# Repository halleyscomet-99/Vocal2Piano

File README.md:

# Vocal2Piano

A robot piano accompanist. A singer sings; a robot sitting on a real keyboard plays the piano part alongside. Two carriages (treble and bass) slide along the keys on stepper motors, each with 13 solenoid fingers.

The app runs in the browser: it loads a song (MIDI or sheet music) or turns a hummed tune into one, plans what the robot can reach and play, and streams it to the robot over USB during rehearsal. With Listen on, the piano follows the singer as it plays: it waits for each entrance, matches the singer's loudness, and moves to the key being sung.

## Repository

| Folder | What's in it |
|---|---|
| [`site/`](site) | The app: React + TypeScript, runs in Chrome or Edge, no install. Start here |
| [`software/`](software) | Offline Python tools: statistics from music datasets (McGill Billboard, POP909) and transcribers for local scores and recordings |
| [`firmware/`](firmware) | Teensy 4.1 firmware (PlatformIO): carriages, solenoids and safety limits, driven by the app over USB ([`PROTOCOL.md`](firmware/PROTOCOL.md)). Its README has the bring-up steps |
| [`hardware/CAD/`](hardware/CAD) | Fusion 360 models of the robot: carriages, fingers, mounts |
| [`hardware/PCB/`](hardware/PCB) | KiCad boards: `C0nTrollER` (Teensy, stepper drivers, power) and `PLAyeRs` (13 solenoid channels each), with fabrication files |
| [`legacy/`](legacy) | The first version (Python pipeline, Max/MSP patch, old firmware), kept for reference |

## Run

```bash
cd site
npm install
npm run dev
```

## Local songs

Scores and recordings to transcribe go in `software/input/`, and the results in `site/local/`. Both folders are git-ignored: transcriptions of other people's songs are for private practice, not for publishing.

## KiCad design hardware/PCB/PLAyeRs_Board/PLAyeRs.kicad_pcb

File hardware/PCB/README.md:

# PCB： Design

| Board | Role | Size | Qty |
|---|---|---|---|
| [**C0nTrollER**](C0nTrollER_Board/) | Main controller: Teensy 4.1, two stepper drivers, power input and protection, 5 V rail | 134.7 × 71.2 mm | 1 |
| [**PLAyeRs**](PLAyeRs_Board/) | Solenoid driver: 13 channels driven by a PCA9685 over I²C | 230.1 × 40.1 mm | 2 (Treble + Bass) |

## System Architecture

```
        12 V DC (5 A supply, barrel jack)
              │
   ┌──────────▼────────────────────────────────────────┐
   │ C0nTrollER                                        │
   │  5 A fuse → SMBJ16A TVS → PMOS reverse-polarity   │
   │  → 12 V rail (4700 µF bulk)                       │
   │  MP1584 buck → 5 V                                │
   │  Teensy 4.1 ─ STEP/DIR/EN ─► TMC2209 ×2 ─► NEMA17 ×2
   │             ◄─ ENDSTOP ×2                         │
   │             ─ I²C (SDA/SCL, 4.7 kΩ pull-ups) ─┐   │
   └───────────────────────────────────────────────┼───┘
         7-pin JST-XH (TREBLE)        7-pin JST-XH (BASS)
                 ▼                              ▼
          ┌─────────────┐                ┌─────────────┐
          │ PLAyeRs     │                │ PLAyeRs     │
          │ PCA9685 0x41│                │ PCA9685 0x40│
          │ 13× IRLZ34N │                │ 13× IRLZ34N │
          └──────┬──────┘                └──────┬──────┘
           13 solenoids                    13 solenoids
```

Both PLAyeRs boards share one I²C bus. The board with the A0 solder jumper bridged is `0x41` (Treble); the one without it is `0x40` (Bass).

### Why these parts
- **One MOSFET per key.** A solenoid needs 12 V at about 0.4 A, far more than any logic pin can supply, so each key has its own logic-level N-MOSFET (IRLZ34N) working as a low-side switch.
- **PCA9685.** It gives 16 PWM outputs over two I²C wires. One chip per player board covers all 13 keys, and the PWM can vary how hard a key is struck.
- **TMC2209.** A very quiet stepper driver, which matters because the robot sits next to a microphone. The Teensy only sends STEP / DIR / EN.
- **MP1584 buck.** Steps 12 V down to 5 V efficiently. A linear regulator would turn the difference into heat.
- **Teensy 4.1.** Fast, with plenty of pins and native USB MIDI for the music software.
- **4 layers.** The inner layers are planes: In1 = GNDPWR, In2 = +12 V. They give wide, low-resistance paths for the solenoid and motor current and keep motor noise away from the logic.
- **Double-sided placement on PLAyeRs.** It keeps the long, narrow board compact. C0nTrollER has every part on the top side.

---

## C0nTrollER Board

[Schematic PDF](C0nTrollER_Board/C0nTrollER.pdf) · [3D model](C0nTrollER_Board/C0nTrollER.step) · [Gerbers](C0nTrollER_Board/output/output.zip)

### Power path
1. 12 V barrel jack (CUI PJ-102AH; the connector is rated 5 A).
2. 5 A slow-blow fuse in a 5×20 mm holder (F1).
3. SMBJ16A TVS diode (CR1) clamps voltage spikes.
4. P-MOSFET (Q1, with gate Zener D1) blocks reverse polarity.
5. 4700 µF bulk capacitor (C1, rated 16 V or more; mind the polarity) keeps 12 V steady when the motors and solenoids switch.
6. MP1584 buck module makes 5 V for the Teensy and the PLAyeRs logic.

> **Before first power-up:** with the Teensy removed, adjust the MP1584 output to 5.0 V. Then cut the VIN–VUSB trace on the underside of the Teensy. Otherwise USB 5 V and the board's 5 V rail are tied together and fight each other.

### Teensy 4.1 pin map

| Function | Treble | Bass |
|---|---|---|
| STEP | 5 | 2 |
| DIR | 6 | 3 |
| EN (active LOW) | 7 | 4 |
| ENDSTOP (`INPUT_PULLUP`, pressed = LOW) | 10 | 8 |

I²C uses `Wire`: SDA = pin 18, SCL = pin 19. The TMC2209 UART is not used; motor current is set with each driver's Vref potentiometer.

## PLAyeRs Board

<!-- TODO: photo of the assembled board, ideally on the carriage with solenoids wired -->

[Schematic PDF](PLAyeRs_Board/PLAyeRs.pdf) · [3D model](PLAyeRs_Board/PLAyeRs.step) · [Gerbers](PLAyeRs_Board/output/output.zip)

### One solenoid channel

```
PCA9685 PWM ─ 100 Ω ─┬─ Gate ┐
                     └─ 10 kΩ ─ GNDPWR      IRLZ34N
12 V ─┬─ solenoid ───────────── Drain       Source ─ GNDPWR
      ├─ SS14 (cathode to 12 V, anode to Drain)   flyback
      └─ 680 Ω ─ LED ───────── Drain         lights while the solenoid is on
```

- The 100 Ω gate resistor limits switching current. The 10 kΩ pull-down holds the MOSFET off when the PWM pin isn't being driven.
- The SS14 diode absorbs the inductive kick when the coil switches off.
- The status LED lights when the MOSFET pulls the drain low, so every strike is visible.
- With no solenoid connected, the drain floats at about 9.8 V; this is normal. With a solenoid connected, the drain idles at about 12 V.

### Solenoid
JF-1039(B): 12 V, about 0.4 A, 10 mm stroke, 25 N at full closure. The force is much lower when the plunger is far from closed. Don't keep a solenoid energized for more than about 2 s.

### Power budget
With all 13 channels on at once, one board draws 13 × 0.4 A ≈ 5.2 A, so both boards together draw about 10 A. A 5 A supply cannot sustain that. Firmware must therefore limit how many fingers fire at the same time: a few at once, with short pulses. In normal playing, strikes last 30–150 ms.

## Manufacturing

| Parameter | Value |
|---|---|
| Layers | 4 (F.Cu / In1.Cu GNDPWR / In2.Cu +12 V / B.Cu) |
| Thickness | 1.6 mm |
| Copper | 1 oz outer (35 µm) |
| Fab | JLCPCB (upload `output/output.zip` from each board folder) |

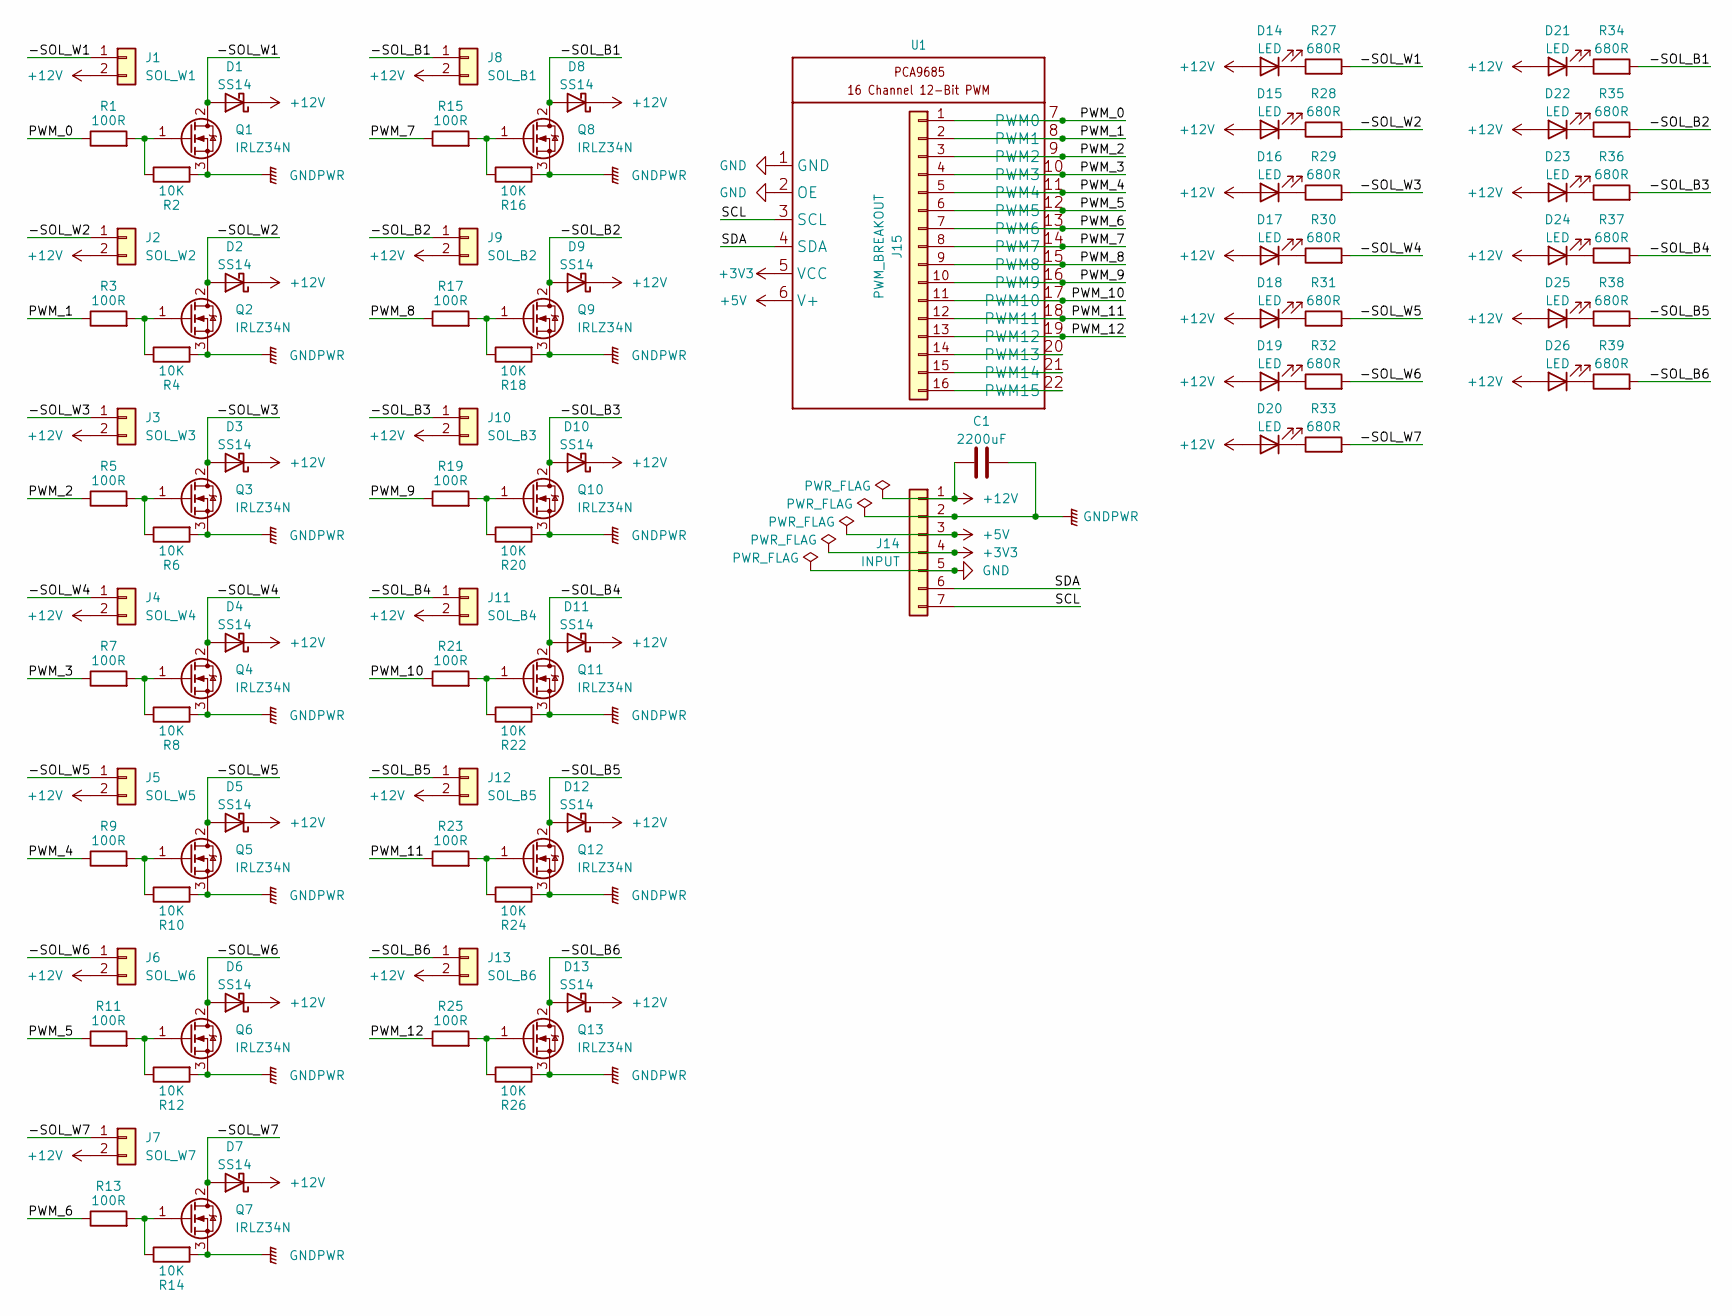
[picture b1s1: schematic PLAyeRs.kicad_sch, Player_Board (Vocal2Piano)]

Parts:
C1: 2200uF; CP_Radial_D16.0mm_P7.50mm
D1, D2, D3, D4, D5, D6, D7, D8, D9, D10, D11, D12, D13: SS14; D_SMA
D14, D15, D16, D17, D18, D19, D20, D21, D22, D23, D24, D25, D26: LED; LED_D5.0mm
J1: SOL_W1; JST_XH_B2B-XH-A_1x02_P2.50mm_Vertical
J2: SOL_W2; JST_XH_B2B-XH-A_1x02_P2.50mm_Vertical
J3: SOL_W3; JST_XH_B2B-XH-A_1x02_P2.50mm_Vertical
J4: SOL_W4; JST_XH_B2B-XH-A_1x02_P2.50mm_Vertical
J5: SOL_W5; JST_XH_B2B-XH-A_1x02_P2.50mm_Vertical
J6: SOL_W6; JST_XH_B2B-XH-A_1x02_P2.50mm_Vertical
J7: SOL_W7; JST_XH_B2B-XH-A_1x02_P2.50mm_Vertical
J8: SOL_B1; JST_XH_B2B-XH-A_1x02_P2.50mm_Vertical
J9: SOL_B2; JST_XH_B2B-XH-A_1x02_P2.50mm_Vertical
J10: SOL_B3; JST_XH_B2B-XH-A_1x02_P2.50mm_Vertical
J11: SOL_B4; JST_XH_B2B-XH-A_1x02_P2.50mm_Vertical
J12: SOL_B5; JST_XH_B2B-XH-A_1x02_P2.50mm_Vertical
J13: SOL_B6; JST_XH_B2B-XH-A_1x02_P2.50mm_Vertical
J14: INPUT; JST_XH_B7B-XH-A_1x07_P2.50mm_Vertical
J15: PWM_BREAKOUT; PinSocket_1x16_P2.54mm_Vertical
Q1, Q2, Q3, Q4, Q5, Q6, Q7, Q8, Q9, Q10, Q11, Q12, Q13: IRLZ34N; TO-220-3_Vertical
R1, R3, R5, R7, R9, R11, R13, R15, R17, R19, R21, R23, R25: 100R; R_0805_2012Metric
R2, R4, R6, R8, R10, R12, R14, R16, R18, R20, R22, R24, R26: 10K; R_0805_2012Metric
R27, R28, R29, R30, R31, R32, R33, R34, R35, R36, R37, R38, R39: 680R; R_0805_2012Metric
U1: Adafruit PCA9685 rev C

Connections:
+3V3: J14.4, U1.5 (VCC)
+5V: J14.3, U1.6 (V+)
+12V: C1.1, D1.1 (K), D2.1 (K), D3.1 (K), D4.1 (K), D5.1 (K), D6.1 (K), D7.1 (K), D8.1 (K), D9.1 (K), D10.1 (K), D11.1 (K), D12.1 (K), D13.1 (K), D14.2 (A), D15.2 (A), D16.2 (A), D17.2 (A), D18.2 (A), D19.2 (A), D20.2 (A), D21.2 (A), D22.2 (A), D23.2 (A), D24.2 (A), D25.2 (A), D26.2 (A), J1.2, J2.2, J3.2, J4.2, J5.2, J6.2, J7.2, J8.2, J9.2, J10.2, J11.2, J12.2, J13.2, J14.1
/-SOL_B1: D8.2 (A), J8.1, Q8.2 (D), R34.2
/-SOL_B2: D9.2 (A), J9.1, Q9.2 (D), R35.2
/-SOL_B3: D10.2 (A), J10.1, Q10.2 (D), R36.2
/-SOL_B4: D11.2 (A), J11.1, Q11.2 (D), R37.2
/-SOL_B5: D12.2 (A), J12.1, Q12.2 (D), R38.2
/-SOL_B6: D13.2 (A), J13.1, Q13.2 (D), R39.2
/-SOL_W1: D1.2 (A), J1.1, Q1.2 (D), R27.2
/-SOL_W2: D2.2 (A), J2.1, Q2.2 (D), R28.2
/-SOL_W3: D3.2 (A), J3.1, Q3.2 (D), R29.2
/-SOL_W4: D4.2 (A), J4.1, Q4.2 (D), R30.2
/-SOL_W5: D5.2 (A), J5.1, Q5.2 (D), R31.2
/-SOL_W6: D6.2 (A), J6.1, Q6.2 (D), R32.2
/-SOL_W7: D7.2 (A), J7.1, Q7.2 (D), R33.2
/PWM_0: J15.1, R1.1, U1.7 (PWM0)
/PWM_1: J15.2, R3.1, U1.8 (PWM1)
/PWM_2: J15.3, R5.1, U1.9 (PWM2)
/PWM_3: J15.4, R7.1, U1.10 (PWM3)
/PWM_4: J15.5, R9.1, U1.11 (PWM4)
/PWM_5: J15.6, R11.1, U1.12 (PWM5)
/PWM_6: J15.7, R13.1, U1.13 (PWM6)
/PWM_7: J15.8, R15.1, U1.14 (PWM7)
/PWM_8: J15.9, R17.1, U1.15 (PWM8)
/PWM_9: J15.10, R19.1, U1.16 (PWM9)
/PWM_10: J15.11, R21.1, U1.17 (PWM10)
/PWM_11: J15.12, R23.1, U1.18 (PWM11)
/PWM_12: J15.13, R25.1, U1.19 (PWM12)
/SCL: J14.7, U1.3 (SCL)
/SDA: J14.6, U1.4 (SDA)
GND: J14.5, U1.1 (GND), U1.2 (OE)
GNDPWR: C1.2, J14.2, Q1.3 (S), Q2.3 (S), Q3.3 (S), Q4.3 (S), Q5.3 (S), Q6.3 (S), Q7.3 (S), Q8.3 (S), Q9.3 (S), Q10.3 (S), Q11.3 (S), Q12.3 (S), Q13.3 (S), R2.2, R4.2, R6.2, R8.2, R10.2, R12.2, R14.2, R16.2, R18.2, R20.2, R22.2, R24.2, R26.2
unnamed: D14.1 (K), R27.1
unnamed: D15.1 (K), R28.1
unnamed: D16.1 (K), R29.1
unnamed: D17.1 (K), R30.1
unnamed: D18.1 (K), R31.1
unnamed: D19.1 (K), R32.1
unnamed: D20.1 (K), R33.1
unnamed: D21.1 (K), R34.1
unnamed: D22.1 (K), R35.1
unnamed: D23.1 (K), R36.1
unnamed: D24.1 (K), R37.1
unnamed: D25.1 (K), R38.1
unnamed: D26.1 (K), R39.1
unnamed: J15.14, U1.20 (PWM13)
unnamed: J15.15, U1.21 (PWM14)
unnamed: J15.16, U1.22 (PWM15)
unnamed: Q1.1 (G), R1.2, R2.1
unnamed: Q2.1 (G), R3.2, R4.1
unnamed: Q3.1 (G), R5.2, R6.1
unnamed: Q4.1 (G), R7.2, R8.1
unnamed: Q5.1 (G), R9.2, R10.1
unnamed: Q6.1 (G), R11.2, R12.1
unnamed: Q7.1 (G), R13.2, R14.1
unnamed: Q8.1 (G), R15.2, R16.1
unnamed: Q9.1 (G), R17.2, R18.1
unnamed: Q10.1 (G), R19.2, R20.1
unnamed: Q11.1 (G), R21.2, R22.1
unnamed: Q12.1 (G), R23.2, R24.1
unnamed: Q13.1 (G), R25.2, R26.1

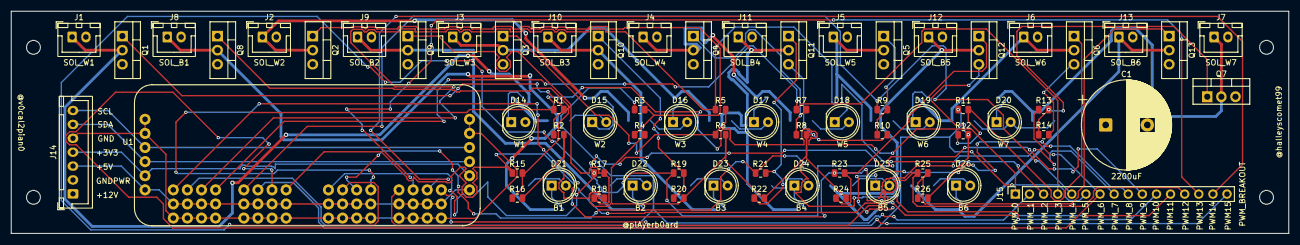
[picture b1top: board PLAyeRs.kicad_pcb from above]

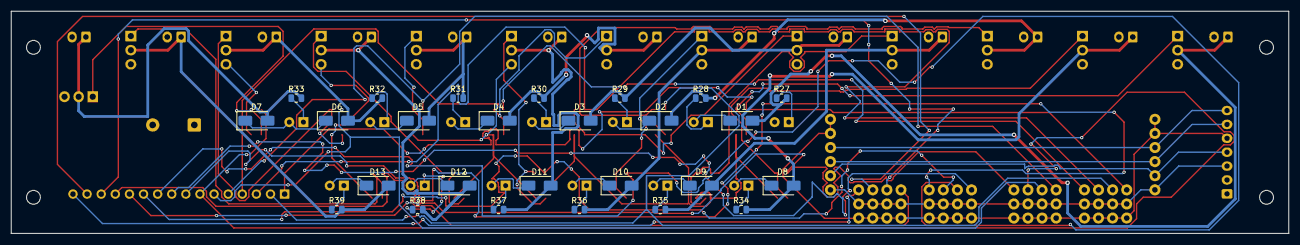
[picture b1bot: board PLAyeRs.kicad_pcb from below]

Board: 4 copper layers, 230.0 x 40.0 mm, 95 parts (26 on the bottom side), 62 nets.

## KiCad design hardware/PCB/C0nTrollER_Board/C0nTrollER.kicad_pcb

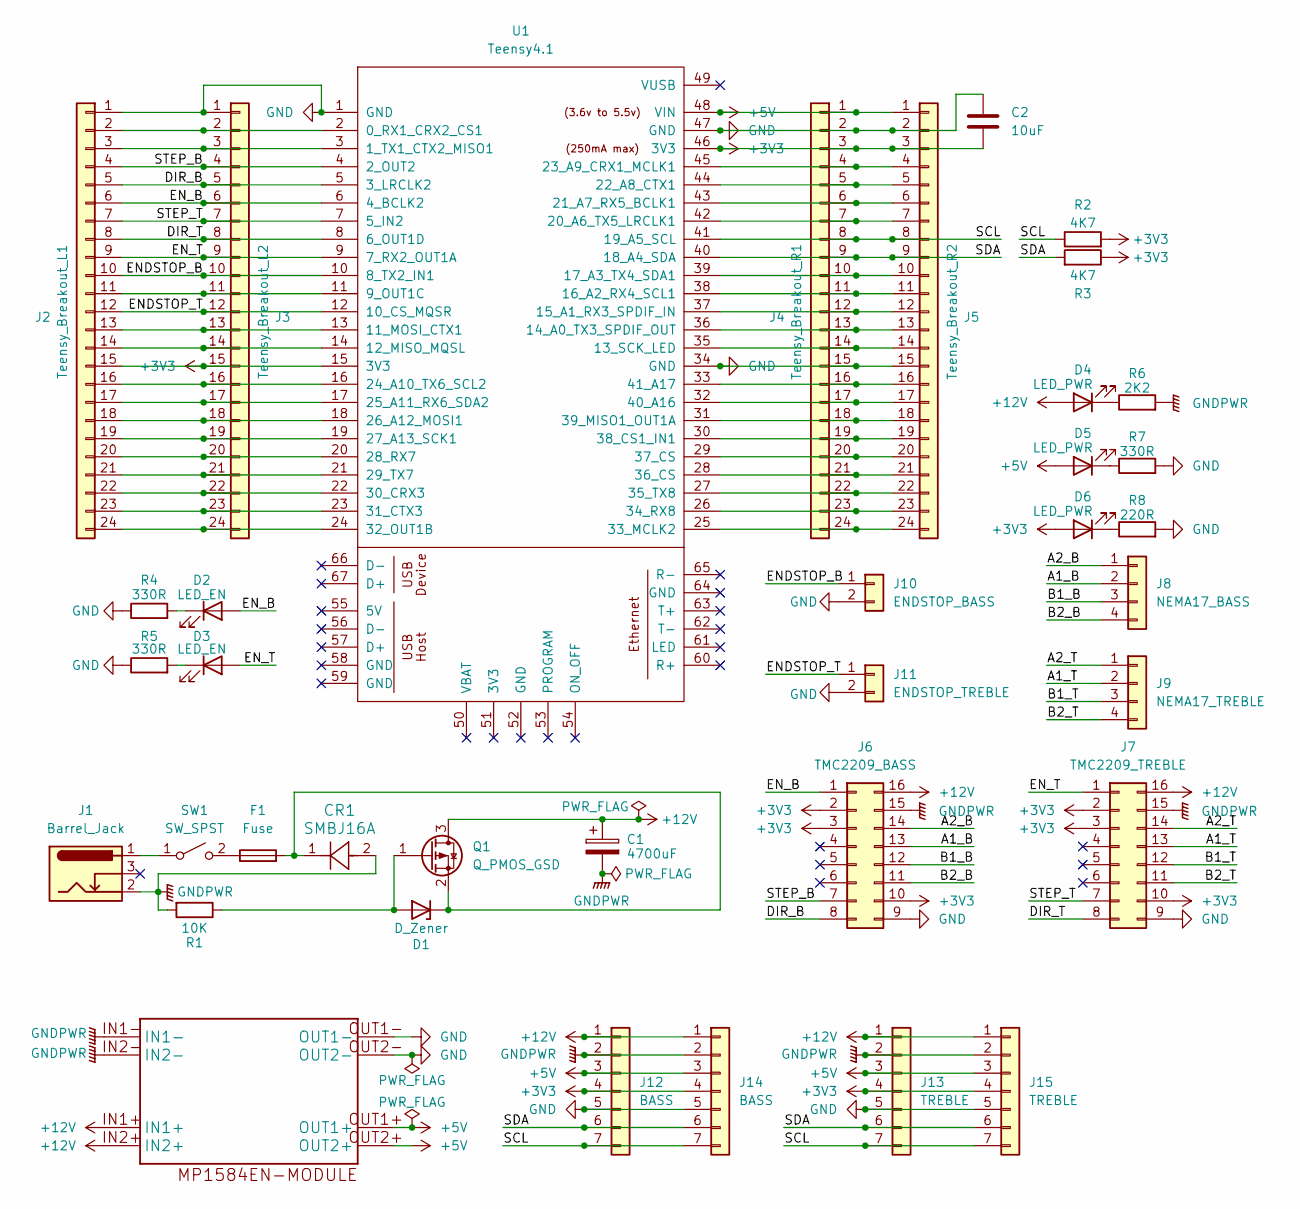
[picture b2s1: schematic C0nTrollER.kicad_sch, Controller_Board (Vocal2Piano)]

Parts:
C1: 4700uF; CP_Radial_D10.0mm_P5.00mm
C2: 10uF; C_0805_2012Metric
CR1: SMBJ16A; SMBJSeries_LTF
D1: D_Zener; D_DO-41_SOD81_P10.16mm_Horizontal
D2, D3: LED_EN; LED_0805_2012Metric
D4, D5, D6: LED_PWR; LED_0805_2012Metric
F1: Fuse; Fuseholder_Cylinder-5x20mm_Bulgin_FX0457_Horizontal_Closed
J1: Barrel_Jack; BarrelJack_CUI_PJ-102AH_Horizontal
J2: Teensy_Breakout_L1; PinSocket_1x24_P2.54mm_Vertical
J3: Teensy_Breakout_L2; PinSocket_1x24_P2.54mm_Vertical
J4: Teensy_Breakout_R1; PinSocket_1x24_P2.54mm_Vertical
J5: Teensy_Breakout_R2; PinSocket_1x24_P2.54mm_Vertical
J6: TMC2209_BASS; Pololu_Breakout-16_15.2x20.3mm
J7: TMC2209_TREBLE; Pololu_Breakout-16_15.2x20.3mm
J8: NEMA17_BASS; PinSocket_1x04_P2.54mm_Vertical
J9: NEMA17_TREBLE; PinSocket_1x04_P2.54mm_Vertical
J10: ENDSTOP_BASS; PinSocket_1x02_P2.54mm_Vertical
J11: ENDSTOP_TREBLE; PinSocket_1x02_P2.54mm_Vertical
J12: BASS; JST_XH_B7B-XH-A_1x07_P2.50mm_Vertical
J13: TREBLE; JST_XH_B7B-XH-A_1x07_P2.50mm_Vertical
J14: BASS; PinSocket_1x07_P2.54mm_Vertical
J15: TREBLE; PinSocket_1x07_P2.54mm_Vertical
MP1584: DSUN_NEW
Q1: Q_PMOS_GSD; SOT-23
R1: 10K; R_0805_2012Metric
R2, R3: 4K7; R_0805_2012Metric
R4, R5, R7: 330R; R_0805_2012Metric
R6: 2K2; R_0805_2012Metric
R8: 220R; R_0805_2012Metric
SW1: SW_SPST; PinSocket_1x02_P2.54mm_Vertical
U1: Teensy4.1; Teensy41

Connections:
+3V3: C2.2, D6.2 (A), J2.15, J3.15, J4.3, J5.3, J6.2, J6.3, J6.10, J7.2, J7.3, J7.10, J12.4, J13.4, J14.4, J15.4, R2.2, R3.1, U1.15 (3V3), U1.46 (3V3)
+5V: D5.2 (A), J4.1, J5.1, J12.3, J13.3, J14.3, J15.3, MP1584.OUT1+, MP1584.OUT2+, U1.48 (VIN)
+12V: C1.1, D4.2 (A), J6.16, J7.16, J12.1, J13.1, J14.1, J15.1, MP1584.IN1+, MP1584.IN2+, Q1.3 (D)
/A1_B: J6.13, J8.2
/A1_T: J7.13, J9.2
/A2_B: J6.14, J8.1
/A2_T: J7.14, J9.1
/B1_B: J6.12, J8.3
/B1_T: J7.12, J9.3
/B2_B: J6.11, J8.4
/B2_T: J7.11, J9.4
/DIR_B: J2.5, J3.5, J6.8, U1.5 (3_LRCLK2)
/DIR_T: J2.8, J3.8, J7.8, U1.8 (6_OUT1D)
/ENDSTOP_B: J2.10, J3.10, J10.1, U1.10 (8_TX2_IN1)
/ENDSTOP_T: J2.12, J3.12, J11.1, U1.12 (10_CS_MQSR)
/EN_B: D2.2 (A), J2.6, J3.6, J6.1, U1.6 (4_BCLK2)
/EN_T: D3.2 (A), J2.9, J3.9, J7.1, U1.9 (7_RX2_OUT1A)
/SCL: J4.8, J5.8, J12.7, J13.7, J14.7, J15.7, R2.1, U1.41 (19_A5_SCL)
/SDA: J4.9, J5.9, J12.6, J13.6, J14.6, J15.6, R3.2, U1.40 (18_A4_SDA)
/STEP_B: J2.4, J3.4, J6.7, U1.4 (2_OUT2)
/STEP_T: J2.7, J3.7, J7.7, U1.7 (5_IN2)
GND: C2.1, J2.1, J3.1, J4.2, J4.15, J5.2, J5.15, J6.9, J7.9, J10.2, J11.2, J12.5, J13.5, J14.5, J15.5, MP1584.OUT1-, MP1584.OUT2-, R4.1, R5.1, R7.2, R8.2, U1.1 (GND), U1.34 (GND), U1.47 (GND)
GNDPWR: C1.2, CR1.2, J1.2, J6.15, J7.15, J12.2, J13.2, J14.2, J15.2, MP1584.IN1-, MP1584.IN2-, R1.2, R6.2
unnamed: D1.2 (A), Q1.1 (G), R1.1
unnamed: CR1.1, D1.1 (K), F1.2, Q1.2 (S)
unnamed: D2.1 (K), R4.2
unnamed: D3.1 (K), R5.2
unnamed: D4.1 (K), R6.1
unnamed: D5.1 (K), R7.1
unnamed: D6.1 (K), R8.1
unnamed: J2.2, J3.2, U1.2 (0_RX1_CRX2_CS1)
unnamed: J2.3, J3.3, U1.3 (1_TX1_CTX2_MISO1)
unnamed: J2.11, J3.11, U1.11 (9_OUT1C)
unnamed: J2.13, J3.13, U1.13 (11_MOSI_CTX1)
unnamed: J2.14, J3.14, U1.14 (12_MISO_MQSL)
unnamed: J2.16, J3.16, U1.16 (24_A10_TX6_SCL2)
unnamed: J2.17, J3.17, U1.17 (25_A11_RX6_SDA2)
unnamed: J2.18, J3.18, U1.18 (26_A12_MOSI1)
unnamed: J2.19, J3.19, U1.19 (27_A13_SCK1)
unnamed: J2.20, J3.20, U1.20 (28_RX7)
unnamed: J2.21, J3.21, U1.21 (29_TX7)
unnamed: J2.22, J3.22, U1.22 (30_CRX3)
unnamed: J2.23, J3.23, U1.23 (31_CTX3)
unnamed: J2.24, J3.24, U1.24 (32_OUT1B)
unnamed: J4.4, J5.4, U1.45 (23_A9_CRX1_MCLK1)
unnamed: J4.5, J5.5, U1.44 (22_A8_CTX1)
unnamed: J4.6, J5.6, U1.43 (21_A7_RX5_BCLK1)
unnamed: J4.7, J5.7, U1.42 (20_A6_TX5_LRCLK1)
unnamed: J4.10, J5.10, U1.39 (17_A3_TX4_SDA1)
unnamed: J4.11, J5.11, U1.38 (16_A2_RX4_SCL1)
unnamed: J4.12, J5.12, U1.37 (15_A1_RX3_SPDIF_IN)
unnamed: J4.13, J5.13, U1.36 (14_A0_TX3_SPDIF_OUT)
unnamed: J4.14, J5.14, U1.35 (13_SCK_LED)
unnamed: J4.16, J5.16, U1.33 (41_A17)
unnamed: J4.17, J5.17, U1.32 (40_A16)
unnamed: J4.18, J5.18, U1.31 (39_MISO1_OUT1A)
unnamed: J4.19, J5.19, U1.30 (38_CS1_IN1)
unnamed: J4.20, J5.20, U1.29 (37_CS)
unnamed: J4.21, J5.21, U1.28 (36_CS)
unnamed: J4.22, J5.22, U1.27 (35_TX8)
unnamed: J4.23, J5.23, U1.26 (34_RX8)
unnamed: J4.24, J5.24, U1.25 (33_MCLK2)
unnamed: J1.1, SW1.1 (A)
unnamed: F1.1, SW1.2 (B)

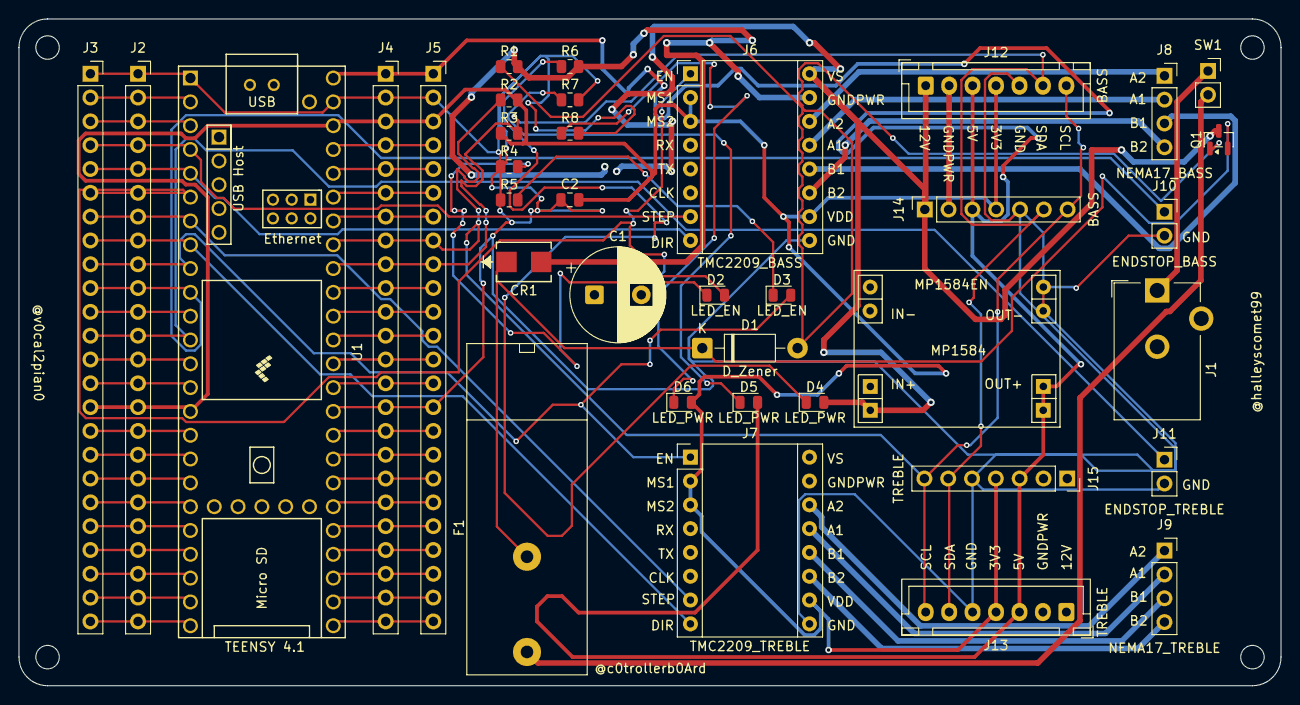
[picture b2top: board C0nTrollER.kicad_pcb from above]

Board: 4 copper layers, 134.6 x 71.1 mm, 37 parts (0 on the bottom side), 64 nets.

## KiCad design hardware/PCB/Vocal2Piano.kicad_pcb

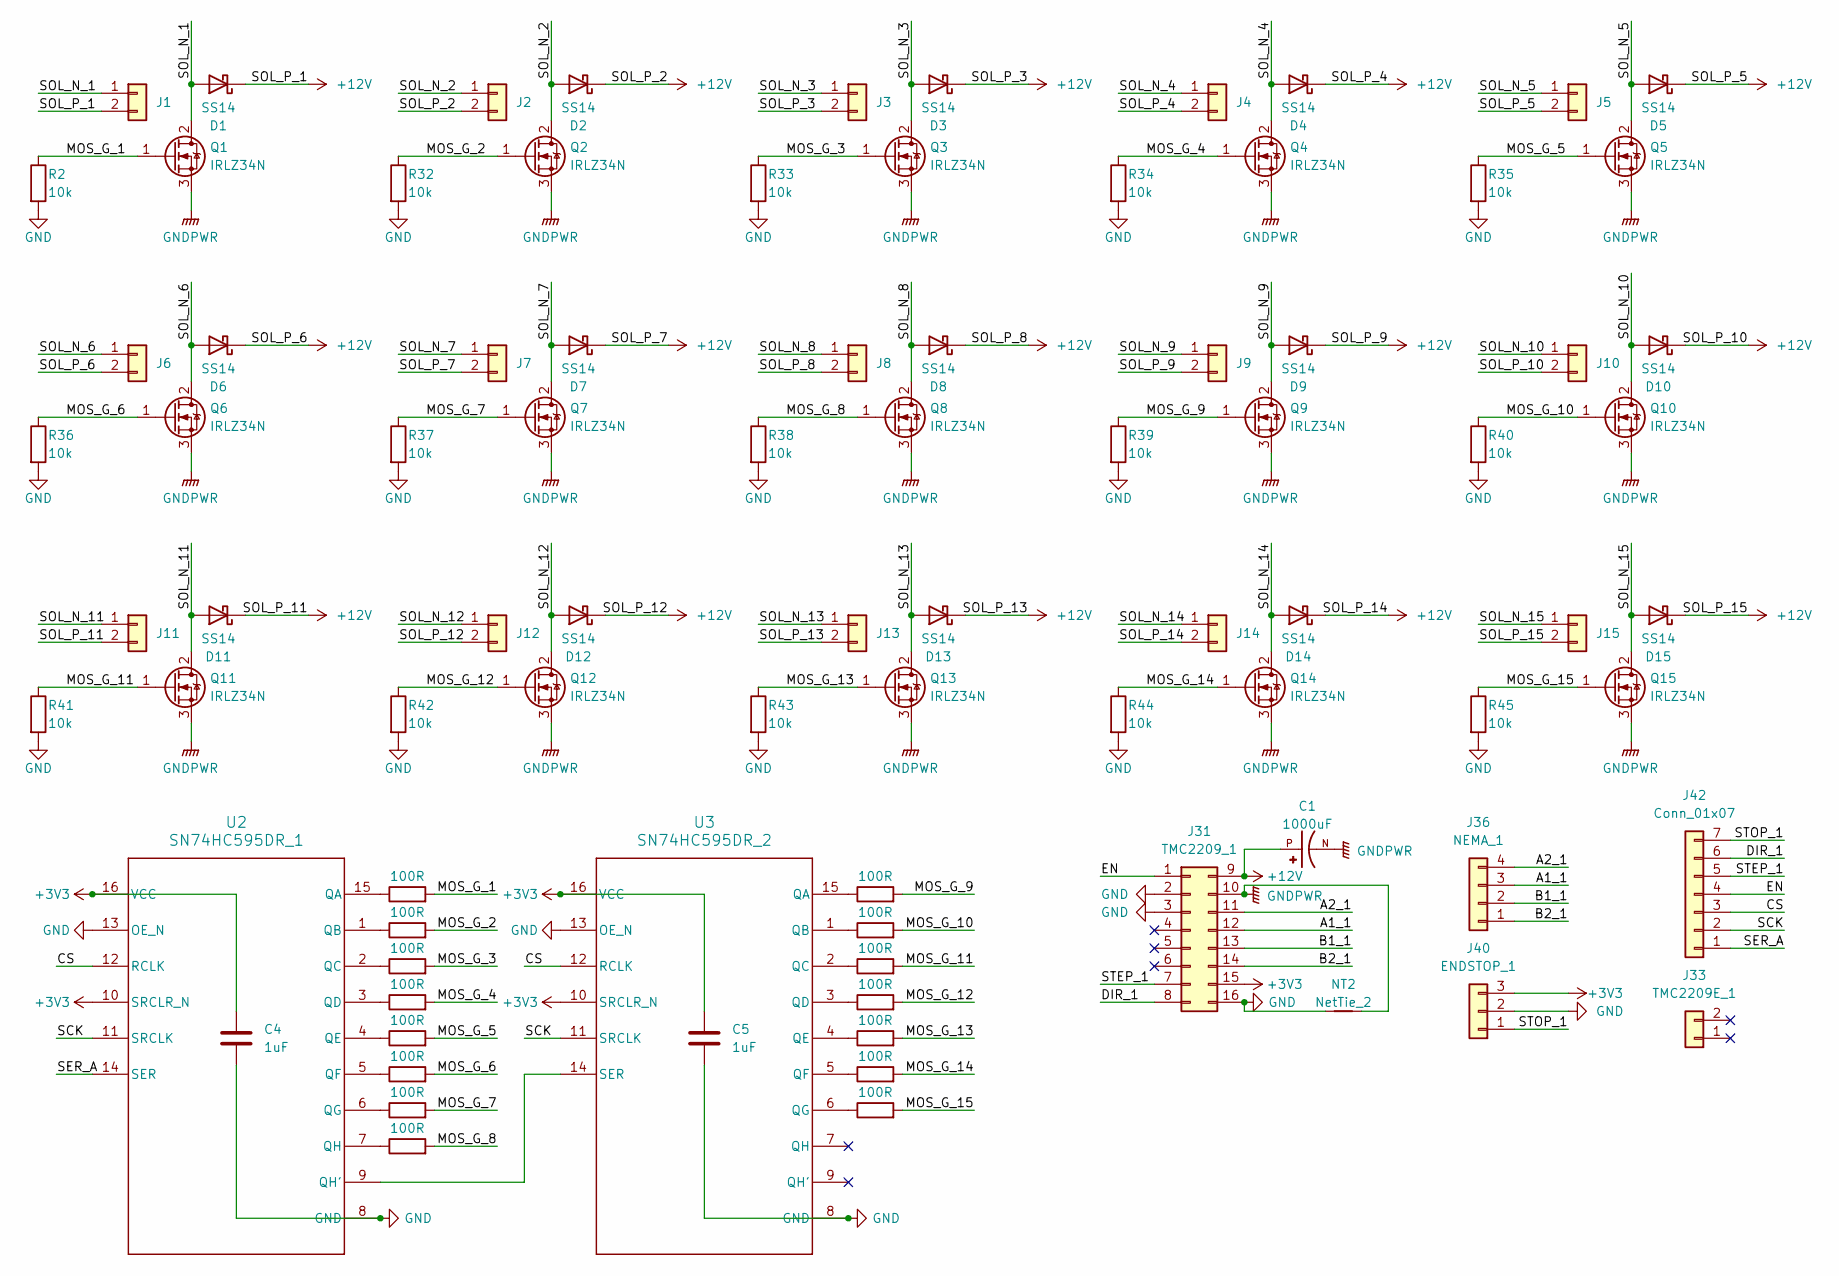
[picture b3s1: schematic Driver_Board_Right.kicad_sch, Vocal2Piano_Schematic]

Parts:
C1: 1000uF; CAPPRD500W60D1250H2000; PARTREV 20-DEC-19
C4, C5: 1uF; C_0805_2012Metric
D1, D2, D3, D4, D5, D6, D7, D8, D9, D10, D11, D12, D13, D14, D15: SS14; D_SMA
J1, J2, J3, J4, J5, J6, J7, J8, J9, J10, J11, J12, J13, J14, J15: Conn_01x02; PinSocket_1x02_P2.54mm_Vertical
J31: TMC2209_1; Pololu_Breakout-16_15.2x20.3mm
J33: TMC2209E_1; PinSocket_1x02_P2.54mm_Vertical
J36: NEMA_1; PinHeader_1x04_P2.54mm_Vertical
J40: ENDSTOP_1; JST_XH_B3B-XH-A_1x03_P2.50mm_Vertical
J42: Conn_01x07; PinSocket_1x07_P2.54mm_Vertical
NT2: NetTie_2; NetTie-2_SMD_Pad0.5mm
Q1, Q2, Q3, Q4, Q5, Q6, Q7, Q8, Q9, Q10, Q11, Q12, Q13, Q14, Q15: IRLZ34N; TO-220-3_Vertical
R1, R3, R4, R5, R6, R7, R8, R9, R10, R11, R12, R13, R14, R15, R16: 100R; R_0805_2012Metric
R2, R32, R33, R34, R35, R36, R37, R38, R39, R40, R41, R42, R43, R44, R45: 10k; R_0805_2012Metric
U2: SN74HC595DR_1; D0016A_N
U3: SN74HC595DR_2; D0016A_N

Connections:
+3V3: C4.1, C5.1, J31.15 (VDD), J40.3, U2.10 (SRCLR_N), U2.16 (VCC), U3.10 (SRCLR_N), U3.16 (VCC); also elsewhere on the board
+12V: C1.P, D1.1 (K), D2.1 (K), D3.1 (K), D4.1 (K), D5.1 (K), D6.1 (K), D7.1 (K), D8.1 (K), D9.1 (K), D10.1 (K), D11.1 (K), D12.1 (K), D13.1 (K), D14.1 (K), D15.1 (K), J1.2, J2.2, J3.2, J4.2, J5.2, J6.2, J7.2, J8.2, J9.2, J10.2, J11.2, J12.2, J13.2, J14.2, J15.2, J31.9 (VM); also elsewhere on the board
/Driver_Board_Right/A1_1: J31.12 (A1), J36.3
/Driver_Board_Right/A2_1: J31.11 (A2), J36.4
/Driver_Board_Right/B1_1: J31.13 (B1), J36.2
/Driver_Board_Right/B2_1: J31.14 (B2), J36.1
/Driver_Board_Right/CS: J42.3, U2.12 (RCLK), U3.12 (RCLK)
/Driver_Board_Right/DIR_1: J31.8 (DIR), J42.6
/Driver_Board_Right/EN: J31.1 (EN), J42.4
/Driver_Board_Right/MOS_G_1: Q1.1 (G), R1.2, R2.1
/Driver_Board_Right/MOS_G_2: Q2.1 (G), R3.2, R32.1
/Driver_Board_Right/MOS_G_3: Q3.1 (G), R4.2, R33.1
/Driver_Board_Right/MOS_G_4: Q4.1 (G), R5.2, R34.1
/Driver_Board_Right/MOS_G_5: Q5.1 (G), R6.2, R35.1
/Driver_Board_Right/MOS_G_6: Q6.1 (G), R7.2, R36.1
/Driver_Board_Right/MOS_G_7: Q7.1 (G), R8.2, R37.1
/Driver_Board_Right/MOS_G_8: Q8.1 (G), R9.2, R38.1
/Driver_Board_Right/MOS_G_9: Q9.1 (G), R10.2, R39.1
/Driver_Board_Right/MOS_G_10: Q10.1 (G), R11.2, R40.1
/Driver_Board_Right/MOS_G_11: Q11.1 (G), R12.2, R41.1
/Driver_Board_Right/MOS_G_12: Q12.1 (G), R13.2, R42.1
/Driver_Board_Right/MOS_G_13: Q13.1 (G), R14.2, R43.1
/Driver_Board_Right/MOS_G_14: Q14.1 (G), R15.2, R44.1
/Driver_Board_Right/MOS_G_15: Q15.1 (G), R16.2, R45.1
/Driver_Board_Right/SCK: J42.2, U2.11 (SRCLK), U3.11 (SRCLK)
/Driver_Board_Right/SER_A: J42.1, U2.14 (SER)
/Driver_Board_Right/SOL_N_1: D1.2 (A), J1.1, Q1.2 (D)
/Driver_Board_Right/SOL_N_2: D2.2 (A), J2.1, Q2.2 (D)
/Driver_Board_Right/SOL_N_3: D3.2 (A), J3.1, Q3.2 (D)
/Driver_Board_Right/SOL_N_4: D4.2 (A), J4.1, Q4.2 (D)
/Driver_Board_Right/SOL_N_5: D5.2 (A), J5.1, Q5.2 (D)
/Driver_Board_Right/SOL_N_6: D6.2 (A), J6.1, Q6.2 (D)
/Driver_Board_Right/SOL_N_7: D7.2 (A), J7.1, Q7.2 (D)
/Driver_Board_Right/SOL_N_8: D8.2 (A), J8.1, Q8.2 (D)
/Driver_Board_Right/SOL_N_9: D9.2 (A), J9.1, Q9.2 (D)
/Driver_Board_Right/SOL_N_10: D10.2 (A), J10.1, Q10.2 (D)
/Driver_Board_Right/SOL_N_11: D11.2 (A), J11.1, Q11.2 (D)
/Driver_Board_Right/SOL_N_12: D12.2 (A), J12.1, Q12.2 (D)
/Driver_Board_Right/SOL_N_13: D13.2 (A), J13.1, Q13.2 (D)
/Driver_Board_Right/SOL_N_14: D14.2 (A), J14.1, Q14.2 (D)
/Driver_Board_Right/SOL_N_15: D15.2 (A), J15.1, Q15.2 (D)
/Driver_Board_Right/STEP_1: J31.7 (STEP), J42.5
/Driver_Board_Right/STOP_1: J40.1, J42.7
GND: C4.2, C5.2, J31.2 (MS1), J31.3 (MS2), J31.16 (GND), J40.2, NT2.1, R2.2, R32.2, R33.2, R34.2, R35.2, R36.2, R37.2, R38.2, R39.2, R40.2, R41.2, R42.2, R43.2, R44.2, R45.2, U2.8 (GND), U2.13 (OE_N), U3.8 (GND), U3.13 (OE_N); also elsewhere on the board
GNDPWR: C1.N, J31.10 (GND), NT2.2, Q1.3 (S), Q2.3 (S), Q3.3 (S), Q4.3 (S), Q5.3 (S), Q6.3 (S), Q7.3 (S), Q8.3 (S), Q9.3 (S), Q10.3 (S), Q11.3 (S), Q12.3 (S), Q13.3 (S), Q14.3 (S), Q15.3 (S); also elsewhere on the board
unnamed: R1.1, U2.15 (QA)
unnamed: R3.1, U2.1 (QB)
unnamed: R4.1, U2.2 (QC)
unnamed: R5.1, U2.3 (QD)
unnamed: R6.1, U2.4 (QE)
unnamed: R7.1, U2.5 (QF)
unnamed: R8.1, U2.6 (QG)
unnamed: U2.9 (QH'), U3.14 (SER)
unnamed: R9.1, U2.7 (QH)
unnamed: R10.1, U3.15 (QA)
unnamed: R11.1, U3.1 (QB)
unnamed: R12.1, U3.2 (QC)
unnamed: R13.1, U3.3 (QD)
unnamed: R14.1, U3.4 (QE)
unnamed: R15.1, U3.5 (QF)
unnamed: R16.1, U3.6 (QG)

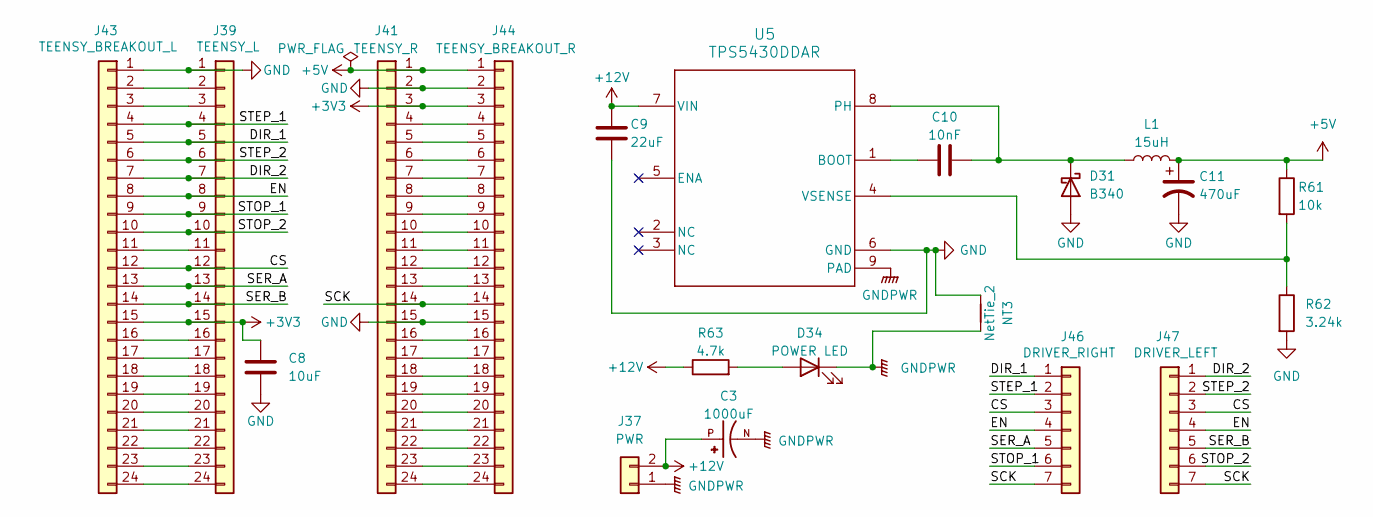
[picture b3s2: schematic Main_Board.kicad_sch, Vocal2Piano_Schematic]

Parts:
C3: 1000uF; CAPPRD500W60D1250H2000; PARTREV 20-DEC-19
C8: 10uF; CP_Radial_D5.0mm_P2.00mm
C9: 22uF; C_1206_3216Metric
C10: 10nF; C_0805_2012Metric
C11: 470uF; CP_Radial_D8.0mm_P3.50mm
D31: B340; D_SMC
D34: POWER LED; LED_0603_1608Metric
J37: PWR; PinSocket_1x02_P2.54mm_Vertical
J39: TEENSY_L; PinSocket_1x24_P2.54mm_Vertical
J41: TEENSY_R; PinSocket_1x24_P2.54mm_Vertical
J43: TEENSY_BREAKOUT_L; PinSocket_1x24_P2.54mm_Vertical
J44: TEENSY_BREAKOUT_R; PinSocket_1x24_P2.54mm_Vertical
J46: DRIVER_RIGHT; PinSocket_1x07_P2.54mm_Vertical
J47: DRIVER_LEFT; PinSocket_1x07_P2.54mm_Vertical
L1: 15uH; L_7.3x7.3_H4.5
NT3: NetTie_2; NetTie-2_SMD_Pad0.5mm
R61: 10k; R_0805_2012Metric
R62: 3.24k; R_0805_2012Metric
R63: 4.7k; R_0805_2012Metric
U5: TPS5430DDAR; DDA0008J_NV

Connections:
+3V3: C8.1, J39.15, J41.3, J43.15, J44.3; also elsewhere on the board
+5V: C11.1, J41.1, J44.1, L1.2, R61.1
+12V: C3.P, C9.1, J37.2, R63.1, U5.7 (VIN); also elsewhere on the board
/Main_Board/CS: J39.12, J43.12, J46.3, J47.3
/Main_Board/DIR_1: J39.5, J43.5, J46.1
/Main_Board/DIR_2: J39.7, J43.7, J47.1
/Main_Board/EN: J39.8, J43.8, J46.4, J47.4
/Main_Board/SCK: J41.14, J44.14, J46.7, J47.7
/Main_Board/SER_A: J39.13, J43.13, J46.5
/Main_Board/SER_B: J39.14, J43.14, J47.5
/Main_Board/STEP_1: J39.4, J43.4, J46.2
/Main_Board/STEP_2: J39.6, J43.6, J47.2
/Main_Board/STOP_1: J39.9, J43.9, J46.6
/Main_Board/STOP_2: J39.10, J43.10, J47.6
GND: C8.2, C9.2, C11.2, D31.2 (A), J39.1, J41.2, J41.15, J43.1, J44.2, J44.15, NT3.1, R62.2, U5.6 (GND); also elsewhere on the board
GNDPWR: C3.N, D34.1 (K), J37.1, NT3.2, U5.9 (PAD); also elsewhere on the board
unnamed: C10.2, D31.1 (K), L1.1, U5.8 (PH)
unnamed: D34.2 (A), R63.2
unnamed: J39.2, J43.2
unnamed: J39.3, J43.3
unnamed: J39.11, J43.11
unnamed: J39.16, J43.16
unnamed: J39.17, J43.17
unnamed: J39.18, J43.18
unnamed: J39.19, J43.19
unnamed: J39.20, J43.20
unnamed: J39.21, J43.21
unnamed: J39.22, J43.22
unnamed: J39.23, J43.23
unnamed: J39.24, J43.24
unnamed: J41.4, J44.4
unnamed: J41.5, J44.5
unnamed: J41.6, J44.6
unnamed: J41.7, J44.7
unnamed: J41.8, J44.8
unnamed: J41.9, J44.9
unnamed: J41.10, J44.10
unnamed: J41.11, J44.11
unnamed: J41.12, J44.12
unnamed: J41.13, J44.13
unnamed: J41.16, J44.16
unnamed: J41.17, J44.17
unnamed: J41.18, J44.18
unnamed: J41.19, J44.19
unnamed: J41.20, J44.20
unnamed: J41.21, J44.21
unnamed: J41.22, J44.22
unnamed: J41.23, J44.23
unnamed: J41.24, J44.24
unnamed: C10.1, U5.1 (BOOT)
unnamed: R61.2, R62.1, U5.4 (VSENSE)
